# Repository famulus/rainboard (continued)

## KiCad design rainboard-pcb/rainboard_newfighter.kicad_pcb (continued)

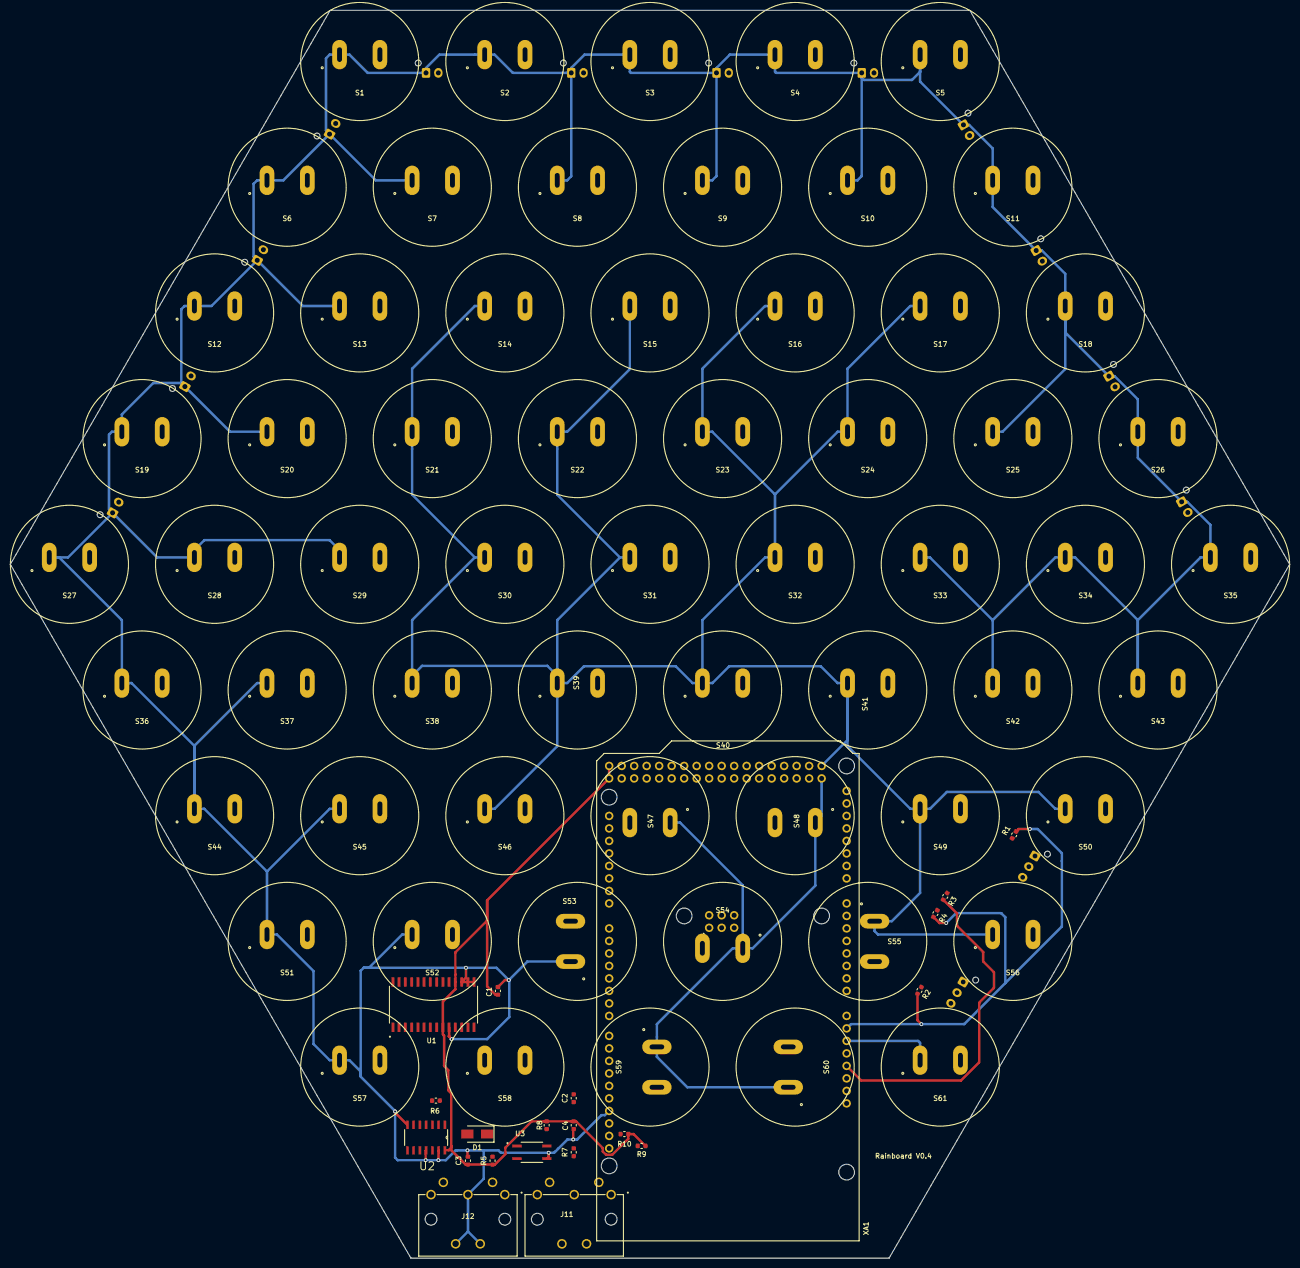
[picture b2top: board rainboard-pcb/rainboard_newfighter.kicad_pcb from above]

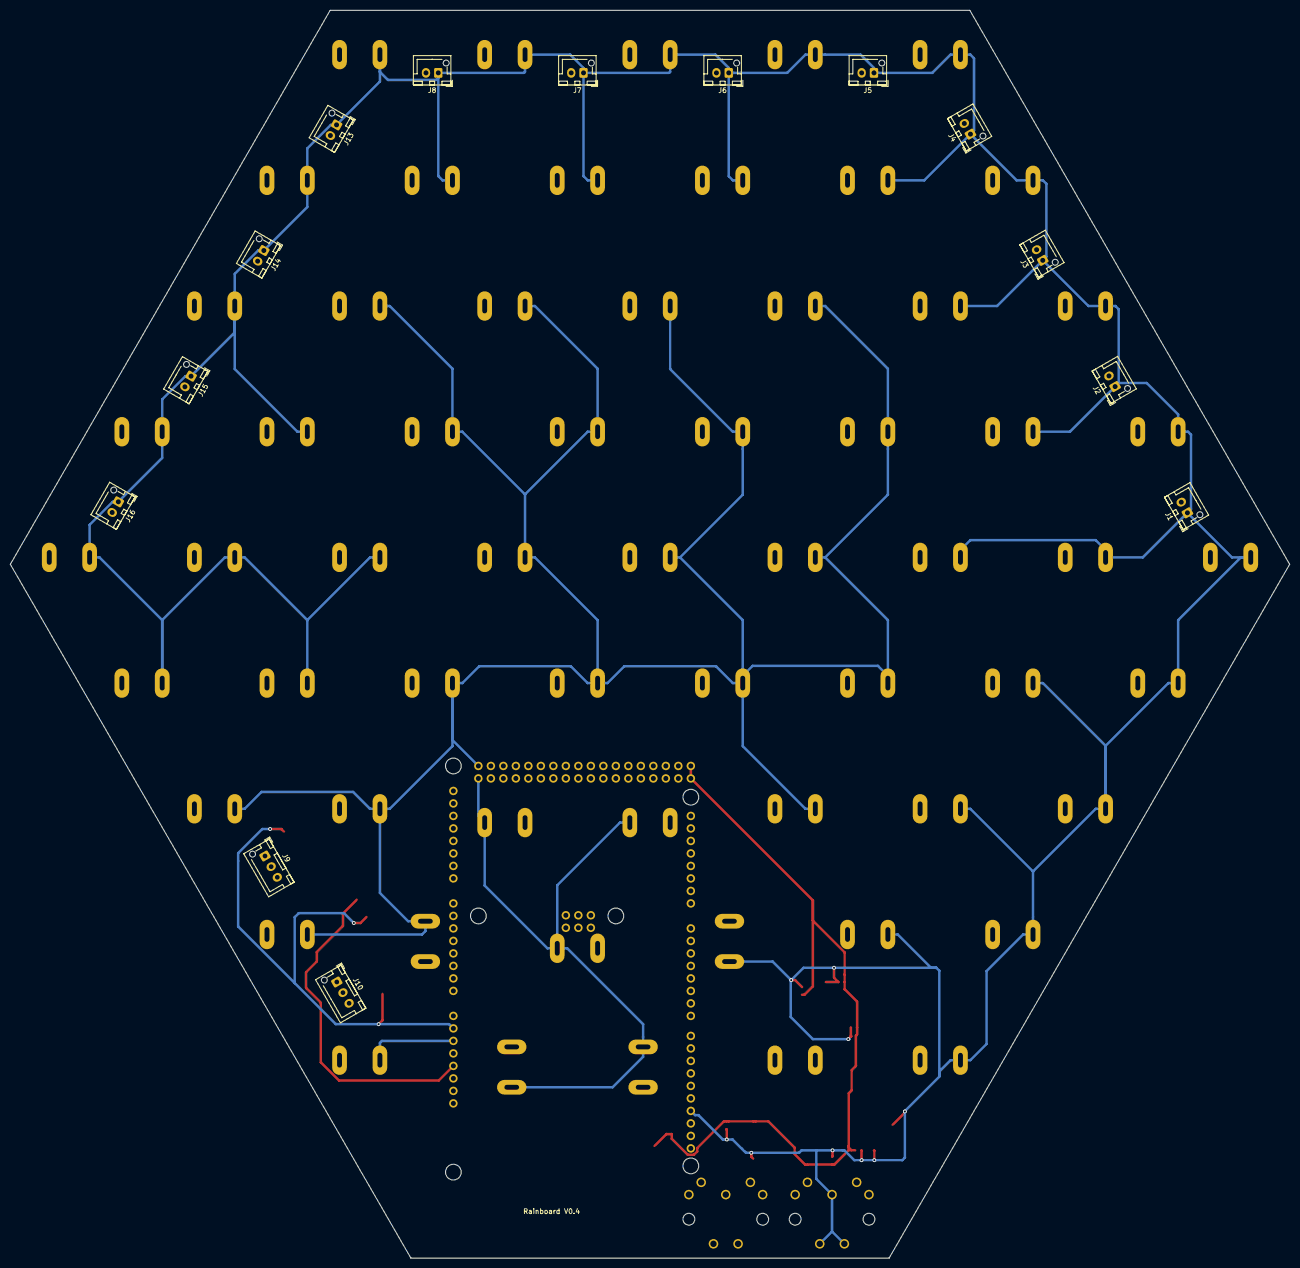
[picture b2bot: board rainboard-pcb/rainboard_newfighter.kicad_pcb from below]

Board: 2 copper layers, 260.0 x 253.6 mm, 96 parts (14 on the bottom side), 95 nets.

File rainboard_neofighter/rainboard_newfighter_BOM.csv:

"Id";"Designator";"Package";"Quantity";"Designation";"Supplier and ref";
1;"J10,J9";"JST_XH_B3B-XH-AM_1x03_P2.50mm_Vertical";2;"Conn_01x03";;;
2;"J18,J17,J16,J15,J14,J13,J8,J7,J6,J5,J4,J3,J2,J1";"JST_XH_B2B-XH-AM_1x02_P2.50mm_Vertical";14;"Conn_01x02";;;
3;"R8";"R_0603_1608Metric";1;"10k";;;
4;"J12,J11";"CUI_SDS-50J";2;"SDS-50J";;;
5;"U3";"SOP254P700X200-4N";1;"EL357N(A)(TA)-G";;;
6;"R7,R6,R5";"R_0603_1608Metric";3;"220R";;;
7;"U1";"SOIC127P1030X265-28N";1;"MCP23017-E_SO";;;
8;"C4,C3,C2,C1";"C_0603_1608Metric";4;"0.1uf";;;
9;"U2";"SOIC127P600X175-14N";1;"74HC14D";;;
10;"R4,R3";"R_0603_1608Metric";2;"4.7k";;;
11;"R2,R1";"R_0603_1608Metric";2;"100k";;;
12;"S48,S60,S59,S53,S55,S41,S39,S47,S40,S1,S2,S3,S4,S5,S6,S7,S8,S9,S10,S11,S12,S13,S14,S15,S16,S17,S18,S19,S20,S21,S22,S23,S24,S25,S26,S27,S28,S29,S30,S31,S32,S33,S34,S35,S36,S37,S38,S42,S43,S44,S45,S46,S49,S50,S51,S52,S54,S56,S57,S58,S61";"Sanwa-OBSF24-v2";61;"SANWA-OBSF24";;;
13;"XA1";"Arduino_Mega2560_Shield";1;"Arduino_Mega2560_Shield";;;

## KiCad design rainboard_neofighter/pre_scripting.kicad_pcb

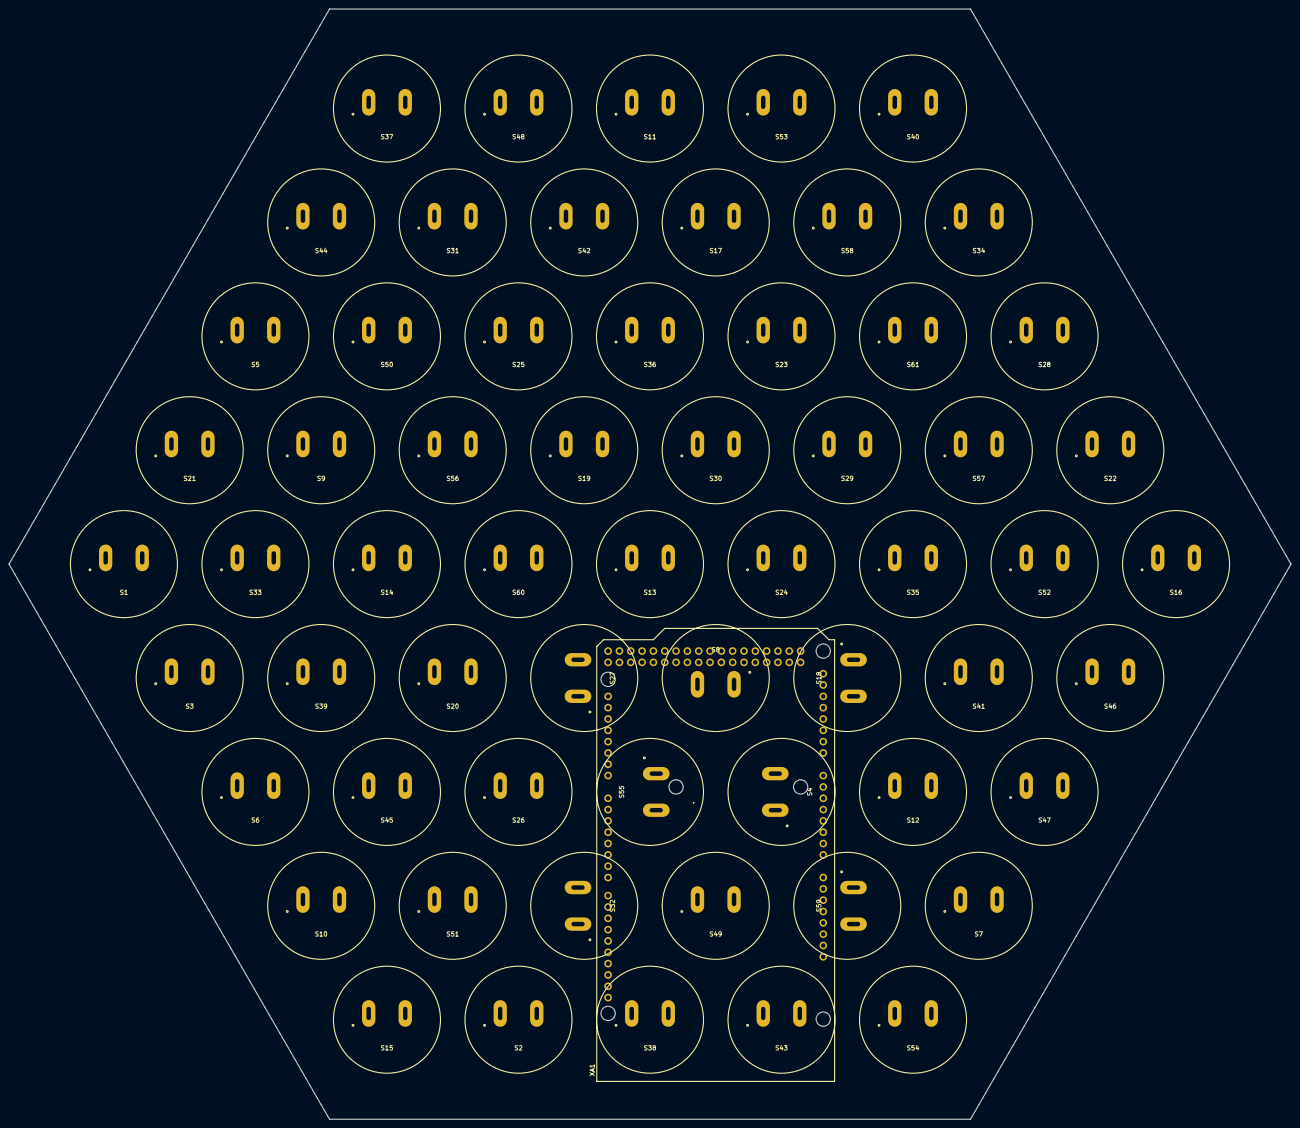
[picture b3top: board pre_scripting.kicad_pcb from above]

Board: 2 copper layers, 287.5 x 249.0 mm, 62 parts (0 on the bottom side), 62 nets, no tracks yet.

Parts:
S1, S2, S3, S4, S5, S6, S7, S8, S9, S10, S11, S12, S13, S14, S15, S16, S17, S18, S19, S20, S21, S22, S23, S24, S25, S26, S27, S28, S29, S30, S31, S32, S33, S34, S35, S36, S37, S38, S39, S40, S41, S42, S43, S44, S45, S46, S47, S48, S49, S50, S51, S52, S53, S54, S55, S56, S57, S58, S59, S60, S61: SANWA-OBSF24; Sanwa-OBSF24
XA1: Arduino_Mega2560_Shield

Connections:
Earth: S1.1, S2.1, S3.1, S4.1, S5.1, S6.1, S7.1, S8.1, S9.1, S10.1, S11.1, S12.1, S13.1, S14.1, S15.1, S16.1, S17.1, S18.1, S19.1, S20.1, S21.1, S22.1, S23.1, S24.1, S25.1, S26.1, S27.1, S28.1, S29.1, S30.1, S31.1, S32.1, S33.1, S34.1, S35.1, S36.1, S37.1, S38.1, S39.1, S40.1, S41.1, S42.1, S43.1, S44.1, S45.1, S46.1, S47.1, S48.1, S49.1, S50.1, S51.1, S52.1, S53.1, S54.1, S55.1, S56.1, S57.1, S58.1, S59.1, S60.1, S61.1, XA1.GND1, XA1.GND2, XA1.GND3, XA1.GND5, XA1.GND6
button-01: S1.2, XA1.D1, XA1.SCL, XA1.SDA
button-02: S2.2, XA1.D2
button-03: S3.2, XA1.D3
button-04: S4.2, XA1.D4
button-05: S5.2, XA1.D5
button-06: S6.2, XA1.D6
button-07: S7.2, XA1.D7
button-08: S8.2, XA1.D8
button-09: S9.2, XA1.D9
button-10: S10.2, XA1.D10
button-11: S11.2, XA1.D11
button-12: S12.2, XA1.D12
button-13: S13.2, XA1.D13
button-14: S14.2, XA1.D14
button-15: S15.2, XA1.D15
button-16: S16.2, XA1.D16
button-17: S17.2, XA1.D17
button-18: S18.2, XA1.D18
button-19: S19.2, XA1.D19
button-20: S20.2, XA1.D20
button-21: S21.2, XA1.D21
button-22: S22.2, XA1.D22
button-23: S23.2, XA1.D23
button-24: S24.2, XA1.D24
button-25: S25.2, XA1.D25
button-26: S26.2, XA1.D26
button-27: S27.2, XA1.D27
button-28: S28.2, XA1.D28
button-29: S29.2, XA1.D29
button-30: S30.2, XA1.D30
button-31: S31.2, XA1.D31
button-32: S32.2, XA1.D32
button-33: S33.2, XA1.D33
button-34: S34.2, XA1.D34
button-35: S35.2, XA1.D35
button-36: S36.2, XA1.D36
button-37: S37.2, XA1.D37
button-38: S38.2, XA1.D38
button-39: S39.2, XA1.D39
button-40: S40.2, XA1.D40
button-41: S41.2, XA1.D41
button-42: S42.2, XA1.D42
button-43: S43.2, XA1.D43
button-44: S44.2, XA1.D44
button-45: S45.2, XA1.D45
button-46: S46.2, XA1.D46
button-47: S47.2, XA1.D47
button-48: S48.2, XA1.D48
button-49: S49.2, XA1.D49
button-50: S50.2, XA1.D50
button-51: S51.2, XA1.D51
button-52: S52.2, XA1.D52
button-53: S53.2, XA1.D53
button-54: S54.2, XA1.A0
button-55: S55.2, XA1.A1
button-56: S56.2, XA1.A2
button-57: S57.2, XA1.A3
button-58: S58.2, XA1.A4
button-59: S59.2, XA1.A5
button-60: S60.2, XA1.A6
button-61: S61.2, XA1.A7

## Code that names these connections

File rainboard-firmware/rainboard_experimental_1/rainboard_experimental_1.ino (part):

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      octaveShift(UP);         // Octave +  
      break;
      
    //// * case 4-7 overlap onto BTNs: // GPIOA.4 used for BTN35 // GPIOA.5 used for BTN27 // GPIOA.6 J17 used for BTN28 // GPIOA.7 J18 used for BTN25
    
    case 8: // GPIOB.0 J1
      semitoneShift(UP);       // Semitone +     
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
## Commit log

2020-04-30 init rainboard repo
2020-08-01 add modified neofighter code
2020-08-19 3D printed openscad rainboard chassis
2020-08-19 starting v2 of PCB
2020-09-14 add kicad
2020-09-14 first draft of v2
2020-09-14 use corrent JST-HX connector
2020-09-17 final board outline dimentions
2020-09-17 move decoupling caps close to ICs
2020-09-17 Add LCSC JLCPCB part data for each component
2020-09-17 Move softpot headers to same corner
2020-09-17 Create analog ground network
2020-09-17 test traces for power and GNDA
2020-09-17 send MINI IN opto signal through schmitt trigger
2020-09-17 fixed broken drill-hole
2020-09-18 v0.2 complete and send to fab
2020-09-20 Fix footprints so centroid file generates correctly
2020-09-20 update 3d chassis
2020-09-20 back panel complete
2020-09-21 V0.2 complete and sent to manufacture
2020-09-28 check in solver for PCB shape
2020-10-06 final checking for v2
2020-10-18 PCB v0.3
2020-10-19 V0.3 candidate
2020-10-22 v3 of chassis and plexi back
2020-10-22 rename a file that was breaking windows
2020-10-22 Create README.md
    An isomorphic MIDI controller.
2020-10-22 remove now unused copy of neofighter-M0v1
2020-10-22 honey-comb: smaller PCB outline
2020-10-22 cleanup project directory
2020-10-22 rename kicad directory, use relative paths in kicad libraries
2020-10-22 Update README.md
    Update Readme
2020-10-23 version 3 firmware
2020-10-23 Cleanup firmware directory
2020-10-26 update readme to use images from github
2020-10-26 re-name neofighter.ino to rainboard_firmware.ino
2020-10-26 dot ino must be withing a folder of the same name
2020-10-26 added gitignore
2020-10-26 Readme update
2020-10-26 Readme update
2020-10-26 v2 button mapping on my default
2020-10-27 rename chassis directory
2020-10-27 clean up misc commands file
2020-10-30 PCB v0.4 notes
2020-10-30 V0.4 PCB notes
2020-10-30 V0.4 exploratory work
2020-10-30 start on v0.4 of PCB
2020-11-01 notes for v4
2020-11-01 fix issues with buttons 25 and 28. Improved ground and power network
2020-11-05 Change velocity params
2020-11-05 move velocity to J13 and J14, fix comparison error
2020-11-08 start v0.4 firmware at v0.4 point
2020-11-11 Autorouted v0.4 with thicker power and earth traces
2020-11-11 readme
2020-11-11 add picture of rainboard
2020-11-11 rainboard images
2020-11-13 invert pitchbend
2020-11-20 update v0.4 firmware
2020-11-23 update lightning spec doc
2020-11-23 update lightning spec
2020-11-23 images
2020-11-23 update spec
2020-12-13 Reorganizes project structure and set's up a local symbol library
2020-12-13 Add CC actions to unused meta-buttons
2020-12-15 Starts new revision, fixes lib path
    Input filtering/protection/etc. ; lots of schematic symbols, most of them paired to a footprint. All saved to project library.
    A few button/RGB combos placed, didn't go 60x yet in case it needs a change.
2020-12-19 Schematic improvements; LED/buttons and MCU
    Creates subsheet for on-board LED/BUTTON and off-board LED/button
    most electrical connections of 2560.
    most electrical connections of arudino front end
    most electrical connections of LED controller.
    Adds ESD protection to MIDI
    lots of TODO/questions in text to see what progress remains.
2020-12-19 Minor lib path change
2020-12-31 Footprint Archival
    Archives footprints from old repo + KICAD libs
2020-12-31 A Few more archived footprints
2020-12-31 Schematic nearly finalized; PCB / footprint started
    -Schematic is nearly finished. Needs some footprint associations and verifications.
    -A few open questions remain.
    -some lib updates to go w/ sch improvements
    -
2021-01-02 Schematic review
    - Updates blocks
    - Removes RGB LEDS from off board
    - Fixes ERC errors
2021-01-06 Minor schematic and library changes
    Fixes some typos; changes oscillators to be common to all MCUs; SMD for MIDI opto input
2021-01-06 Minor schematic and library changes
    Identical to previous commit, some files weren't saved.
2021-01-07 Changes Micro USB to USB B
2021-01-07 adds power flag to GNDA
    GNDA was failing ERC check. adds a power flag to fix it
2021-01-13 Removed RGB from buttons, part numbers updated, cleaned up schematic
2021-01-13 New footprints added
    Updated library format for footprints. Pending sync with layout to add all new footprints
2021-01-14 Fixing annotations for buttons and meta buttons
2021-01-14 Moves meta buttons to correct config, adds back on board buttons.
2021-01-14 position midi DIN, USB, and power barrel
2021-01-14 position J4 through J16
2021-01-18 Footprints fixed, button orgin moved to allow placement of LEDs
2021-01-18 Swaps over to 5V input supply
2021-01-19 Modified electrolytics and setup board for layout
2021-01-19 Forgot to update electrolytic PN
2021-01-19 Buttons modified for dimensions
2021-01-20 Starts PCB setup
2021-01-22 general placement of leds
2021-01-23 prelim place & route
    deleted extra R's layout & sch
2021-01-25 routing progress
2021-01-29 Moves meta button connectors to correct spots
    Updates locations for layout to continue
2021-02-02 add website directory
2021-02-03 add website
2021-02-03 Bump elliptic from 6.5.2 to 6.5.4 in /website
    Bumps [elliptic](https://github.com/indutny/elliptic) from 6.5.2 to 6.5.4.
    - [Release notes](https://github.com/indutny/elliptic/releases)
    - [Commits](https://github.com/indutny/elliptic/compare/v6.5.2...v6.5.4)
2021-02-03 Bump lodash from 4.17.15 to 4.17.20 in /website
    Bumps [lodash](https://github.com/lodash/lodash) from 4.17.15 to 4.17.20.
    - [Release notes](https://github.com/lodash/lodash/releases)
    - [Commits](https://github.com/lodash/lodash/compare/4.17.15...4.17.20)
2021-02-03 styling
2021-02-03 update copy
2021-02-03 style updates
2021-02-04 update Surge instructions
2021-02-04 minor style tweak
2021-02-06 position the interfaces, first pass
2021-02-11 routing
    button array routing complete
2021-02-15 route complete
2021-02-18 move metabuttons, position rear jacks, reduce profile of lightning chassis
2021-02-18 thunder chassis with regular hexagon and snap fit
2021-02-18 thunder chassis with non-regular hexagon
2021-02-18 re-organize chassis folder into lightning and thunder
2021-02-18 reduce size of thunder chassis
2021-02-21 Review and gerber export of v1a
2021-02-22 silkscreen updates
2021-02-22 Exports Gerbers and final review
2021-02-26 update website
2021-02-26 git ignore
2021-02-26 update resolution
2021-03-16 ignore DS_Store
2021-03-16 update website: improve picture
2021-03-16 thunder chassis: improve clips
2021-03-22 website: add link to wikipedia
2021-05-24 saving WIP
2021-05-24 add Thunder firmware
2022-03-29 Bump minimist from 1.2.5 to 1.2.6 in /website
    Bumps [minimist](https://github.com/substack/minimist) from 1.2.5 to 1.2.6.
    - [Release notes](https://github.com/substack/minimist/releases)
    - [Commits](https://github.com/substack/minimist/compare/1.2.5...1.2.6)
    ---
    updated-dependencies:
    - dependency-name: minimist
2022-11-10 Bump minimatch from 3.0.4 to 3.1.2 in /website
    Bumps [minimatch](https://github.com/isaacs/minimatch) from 3.0.4 to 3.1.2.
    - [Release notes](https://github.com/isaacs/minimatch/releases)
    - [Commits](https://github.com/isaacs/minimatch/compare/v3.0.4...v3.1.2)
    ---
    updated-dependencies:
    - dependency-name: minimatch
2022-12-07 Bump decode-uri-component from 0.2.0 to 0.2.2 in /website
    Bumps [decode-uri-component](https://github.com/SamVerschueren/decode-uri-component) from 0.2.0 to 0.2.2.
    - [Release notes](https://github.com/SamVerschueren/decode-uri-component/releases)
    - [Commits](https://github.com/SamVerschueren/decode-uri-component/compare/v0.2.0...v0.2.2)
    ---
    updated-dependencies:
    - dependency-name: decode-uri-component
2022-12-12 Bump qs from 6.5.2 to 6.5.3 in /website
    Bumps [qs](https://github.com/ljharb/qs) from 6.5.2 to 6.5.3.
    - [Release notes](https://github.com/ljharb/qs/releases)
    - [Changelog](https://github.com/ljharb/qs/blob/main/CHANGELOG.md)
    - [Commits](https://github.com/ljharb/qs/compare/v6.5.2...v6.5.3)
    ---
    updated-dependencies:
2023-01-07 Bump json5 from 1.0.1 to 1.0.2 in /website
    Bumps [json5](https://github.com/json5/json5) from 1.0.1 to 1.0.2.
    - [Release notes](https://github.com/json5/json5/releases)
    - [Changelog](https://github.com/json5/json5/blob/main/CHANGELOG.md)
    - [Commits](https://github.com/json5/json5/compare/v1.0.1...v1.0.2)
    ---
    updated-dependencies:
2023-03-05 Bump minimist from 1.2.5 to 1.2.8 in /website
    Bumps [minimist](https://github.com/minimistjs/minimist) from 1.2.5 to 1.2.8.
    - [Release notes](https://github.com/minimistjs/minimist/releases)
    - [Changelog](https://github.com/minimistjs/minimist/blob/main/CHANGELOG.md)
    - [Commits](https://github.com/minimistjs/minimist/compare/v1.2.5...v1.2.8)
    ---
    updated-dependencies:
